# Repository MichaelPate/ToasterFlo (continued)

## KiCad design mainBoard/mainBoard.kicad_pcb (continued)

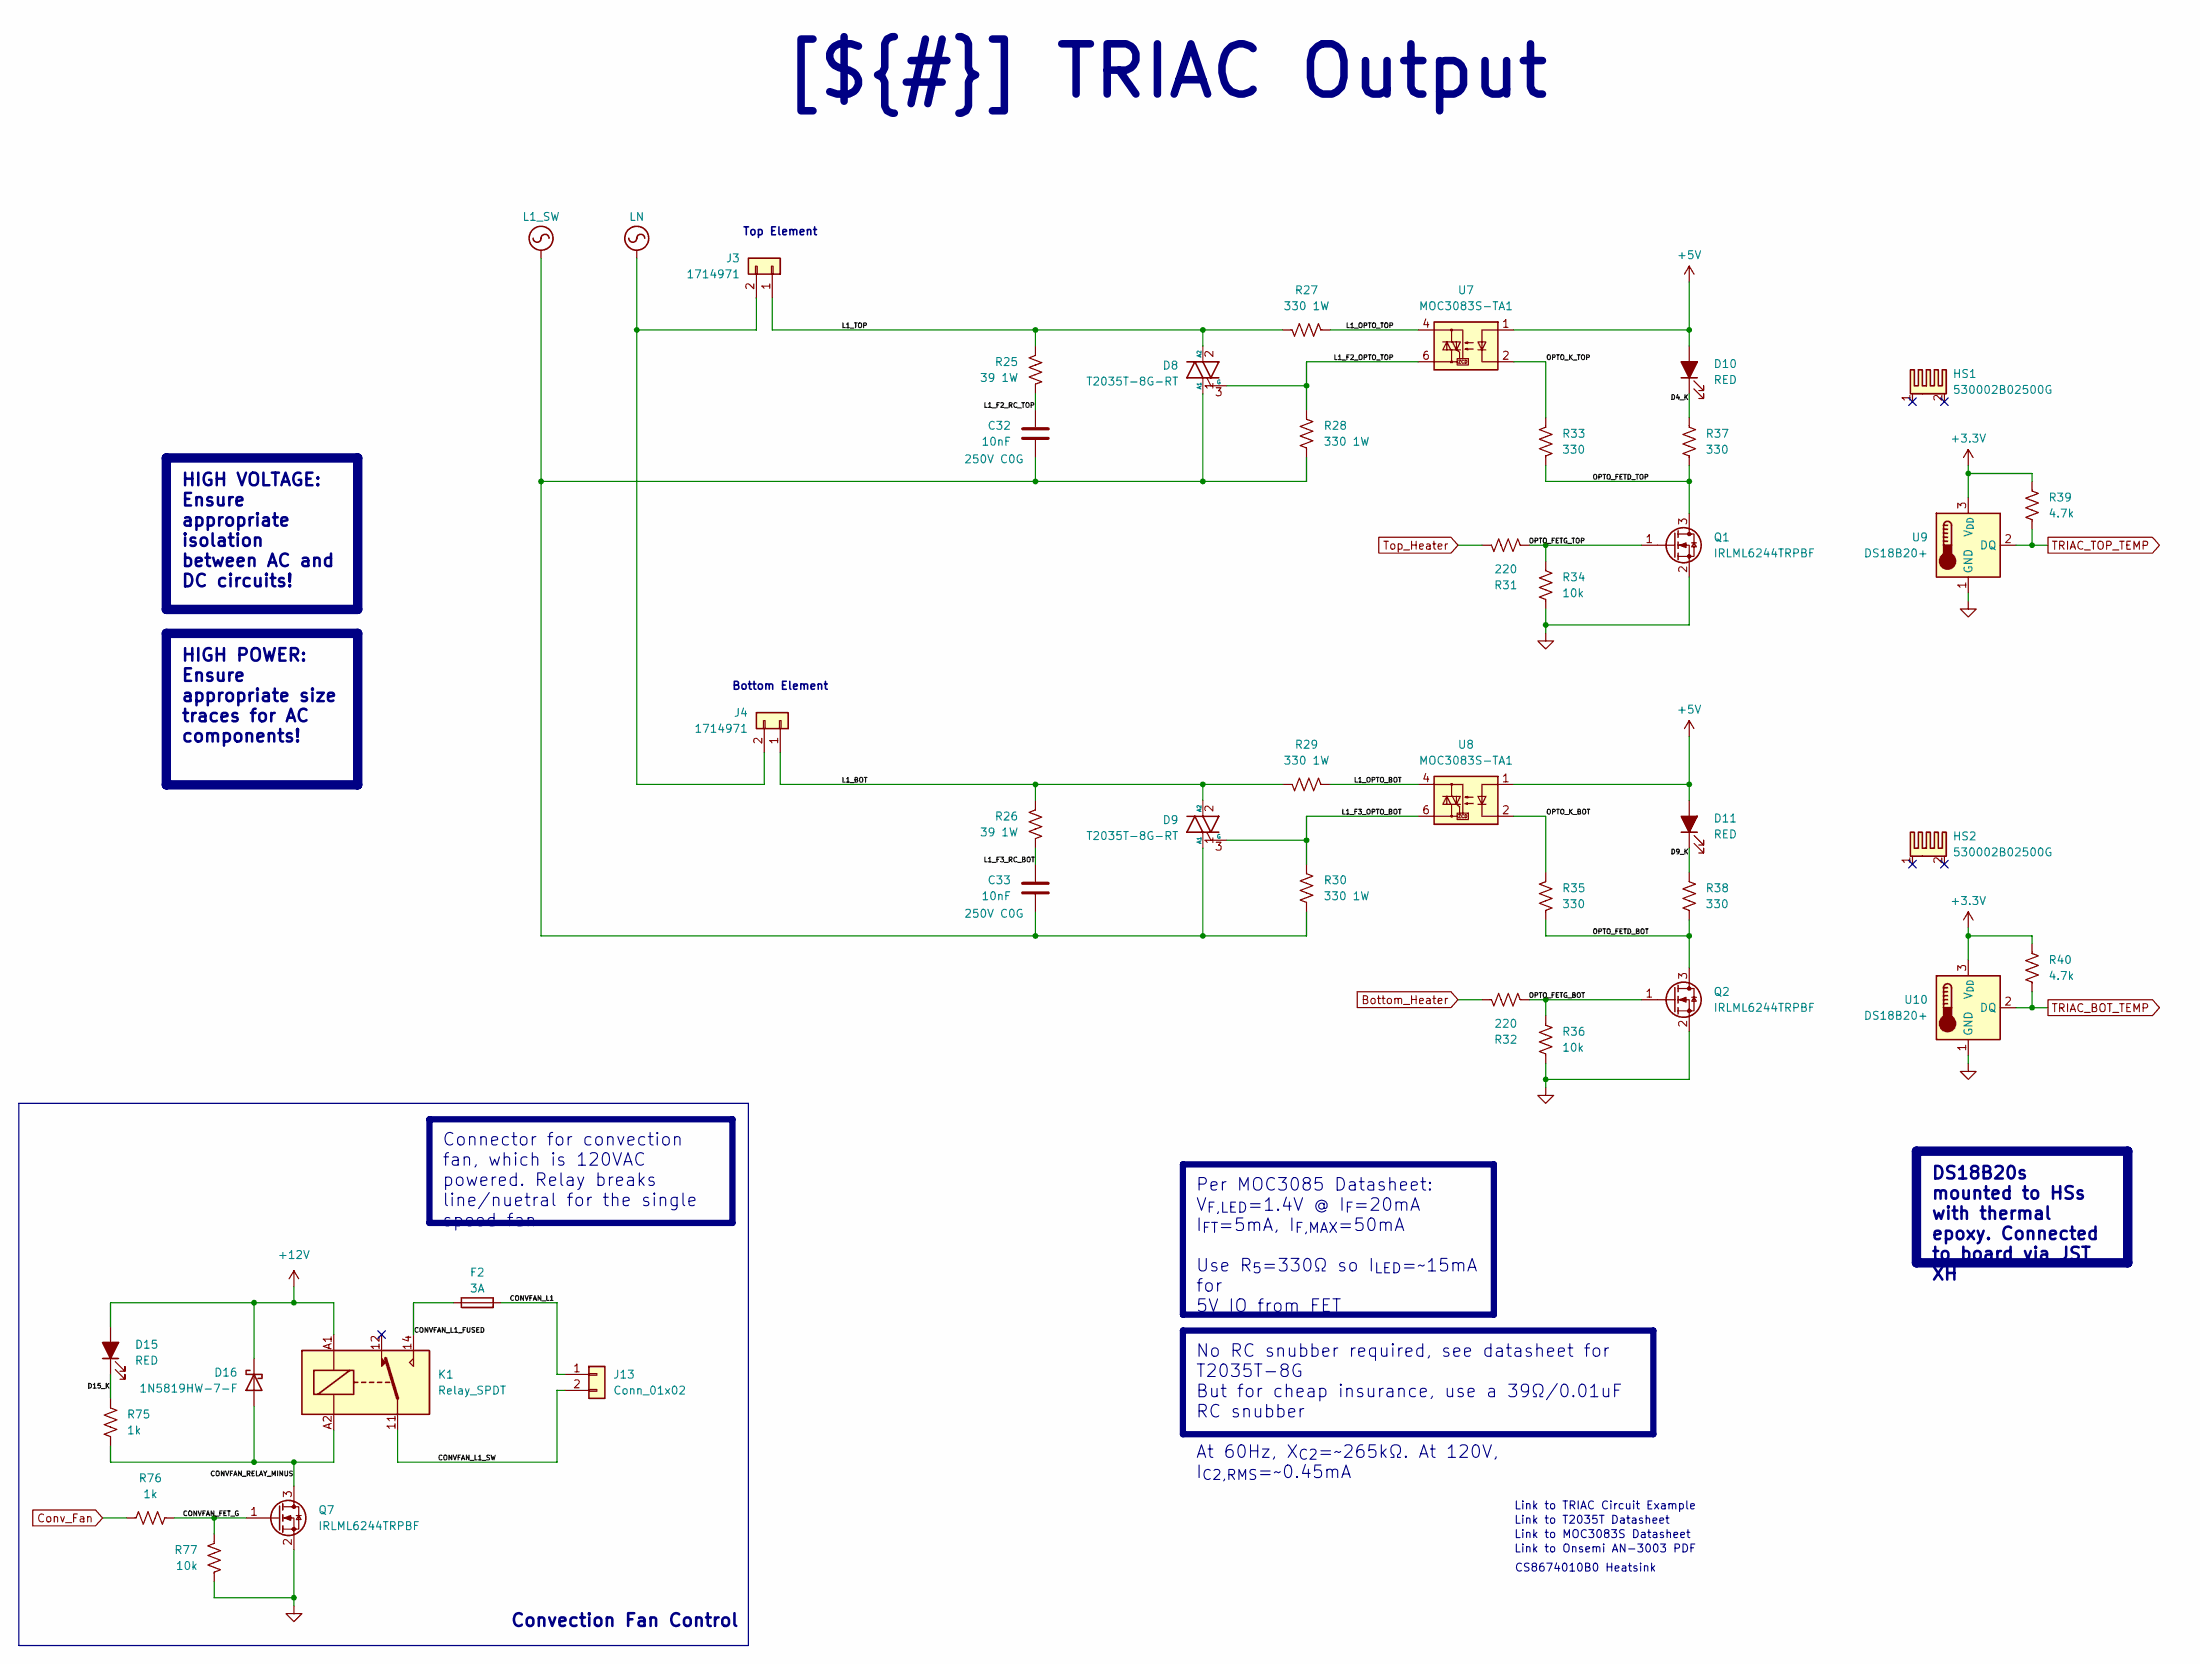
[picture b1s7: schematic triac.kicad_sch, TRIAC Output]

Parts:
C32, C33: 10nF; C_1812_4532Metric_Pad1.57x3.40mm_HandSolder
D8, D9: T2035T-8G-RT; TO-220-3_Vertical
D10, D11, D15: RED; LED_0603_1608Metric_Pad1.05x0.95mm_HandSolder
D16: 1N5819HW-7-F; D_SOD-123
F2: 3A; Fuseholder_Clip-5x20mm_Littelfuse_100_Inline_P20.50x4.60mm_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
HS1, HS2: 530002B02500G; 53002B02500G
J3, J4: 1714971; CONN_1714971_PXC
J13: Conn_01x02; CONN_1714971_PXC
K1: Relay_SPDT; Relay_SPDT_Finder_36.11
Q1, Q2, Q7: IRLML6244TRPBF; SOT-23
R25, R26: 39 1W; R_2512_6332Metric_Pad1.40x3.35mm_HandSolder
R27, R28, R29, R30: 330 1W; R_2512_6332Metric_Pad1.40x3.35mm_HandSolder
R31, R32: 220; R_0603_1608Metric_Pad0.98x0.95mm_HandSolder
R33, R35, R37, R38: 330; R_0603_1608Metric_Pad0.98x0.95mm_HandSolder
R34, R36, R77: 10k; R_0603_1608Metric_Pad0.98x0.95mm_HandSolder
R39, R40: 4.7k; R_0603_1608Metric_Pad0.98x0.95mm_HandSolder
R75, R76: 1k; R_0603_1608Metric_Pad0.98x0.95mm_HandSolder
U7, U8: MOC3083S-TA1; SMDIP-6_W9.53mm
U9, U10: DS18B20+; JST_XH_B3B-XH-A_1x03_P2.50mm_Vertical

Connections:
+3.3V: R39.1, R40.1, U9.3 (V_{DD}), U10.3 (V_{DD}); also elsewhere on the board
+5V: D10.2 (A), D11.2 (A), U7.1, U8.1; also elsewhere on the board
+12V: D15.2 (A), D16.1 (K), K1.A1; also elsewhere on the board
/Project Architecture/TRIAC/CONVFAN_FET_G: Q7.1 (G), R76.2, R77.1
/Project Architecture/TRIAC/CONVFAN_L1: F2.2, J13.1
/Project Architecture/TRIAC/CONVFAN_L1_FUSED: F2.1, K1.14
/Project Architecture/TRIAC/CONVFAN_L1_SW: J13.2, K1.11
/Project Architecture/TRIAC/CONVFAN_RELAY_MINUS: D16.2 (A), K1.A2, Q7.3 (D), R75.2
/Project Architecture/TRIAC/D4_K: D10.1 (K), R37.1
/Project Architecture/TRIAC/D9_K: D11.1 (K), R38.1
/Project Architecture/TRIAC/D15_K: D15.1 (K), R75.1
/Project Architecture/TRIAC/L1_BOT: D9.2 (A2), J4.1, R26.2, R29.2
/Project Architecture/TRIAC/L1_F2_OPTO_TOP: D8.3 (G), R28.2, U7.6
/Project Architecture/TRIAC/L1_F2_RC_TOP: C32.1, R25.1
/Project Architecture/TRIAC/L1_F3_OPTO_BOT: D9.3 (G), R30.2, U8.6
/Project Architecture/TRIAC/L1_F3_RC_BOT: C33.1, R26.1
/Project Architecture/TRIAC/L1_OPTO_BOT: R29.1, U8.4
/Project Architecture/TRIAC/L1_OPTO_TOP: R27.1, U7.4
/Project Architecture/TRIAC/L1_TOP: D8.2 (A2), J3.1, R25.2, R27.2
/Project Architecture/TRIAC/OPTO_FETD_BOT: Q2.3 (D), R35.2, R38.2
/Project Architecture/TRIAC/OPTO_FETD_TOP: Q1.3 (D), R33.2, R37.2
/Project Architecture/TRIAC/OPTO_FETG_BOT: Q2.1 (G), R32.2, R36.1
/Project Architecture/TRIAC/OPTO_FETG_TOP: Q1.1 (G), R31.2, R34.1
/Project Architecture/TRIAC/OPTO_K_BOT: R35.1, U8.2
/Project Architecture/TRIAC/OPTO_K_TOP: R33.1, U7.2
Bottom_Heater: R32.1
Conv_Fan: R76.1
GND: Q1.2 (S), Q2.2 (S), Q7.2 (S), R34.2, R36.2, R77.2, U9.1 (GND), U10.1 (GND); also elsewhere on the board
L1_SW: C32.2, C33.2, D8.1 (A1), D9.1 (A1), R28.1, R30.1; also elsewhere on the board
LN: J3.2, J4.2; also elsewhere on the board
TRIAC_BOT_TEMP: R40.2, U10.2 (DQ)
TRIAC_TOP_TEMP: R39.2, U9.2 (DQ)
Top_Heater: R31.1

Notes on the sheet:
Bottom Element
Link to T2035T Datasheet
Convection Fan Control
CS8674010B0 Heatsink
Link to Onsemi AN-3003 PDF
Top Element
Link to TRIAC Circuit Example
Link to MOC3083S Datasheet
HIGH POWER: Ensure appropriate size traces for AC components!
DS18B20s mounted to HSs with thermal epoxy. Connected to board via JST XH
[${#}] ${TITLE}
Connector for convection fan, which is 120VAC powered. Relay breaks line/nuetral for the single speed fan
HIGH VOLTAGE: Ensure appropriate isolation between AC and DC circuits!
No RC snubber required, see datasheet for T2035T-8G But for cheap insurance, use a 39Ω/0.01uF RC snubber At 60Hz, X_{C2}=~265kΩ. At 120V, I_{C2,RMS}=~0.45mA
Per MOC3085 Datasheet: V_{F,LED}=1.4V @ I_{F}=20mA I_{FT}=5mA, I_{F,MAX}=50mA Use R_{5}=330Ω so I_{LED}=~15mA for 5V IO from FET

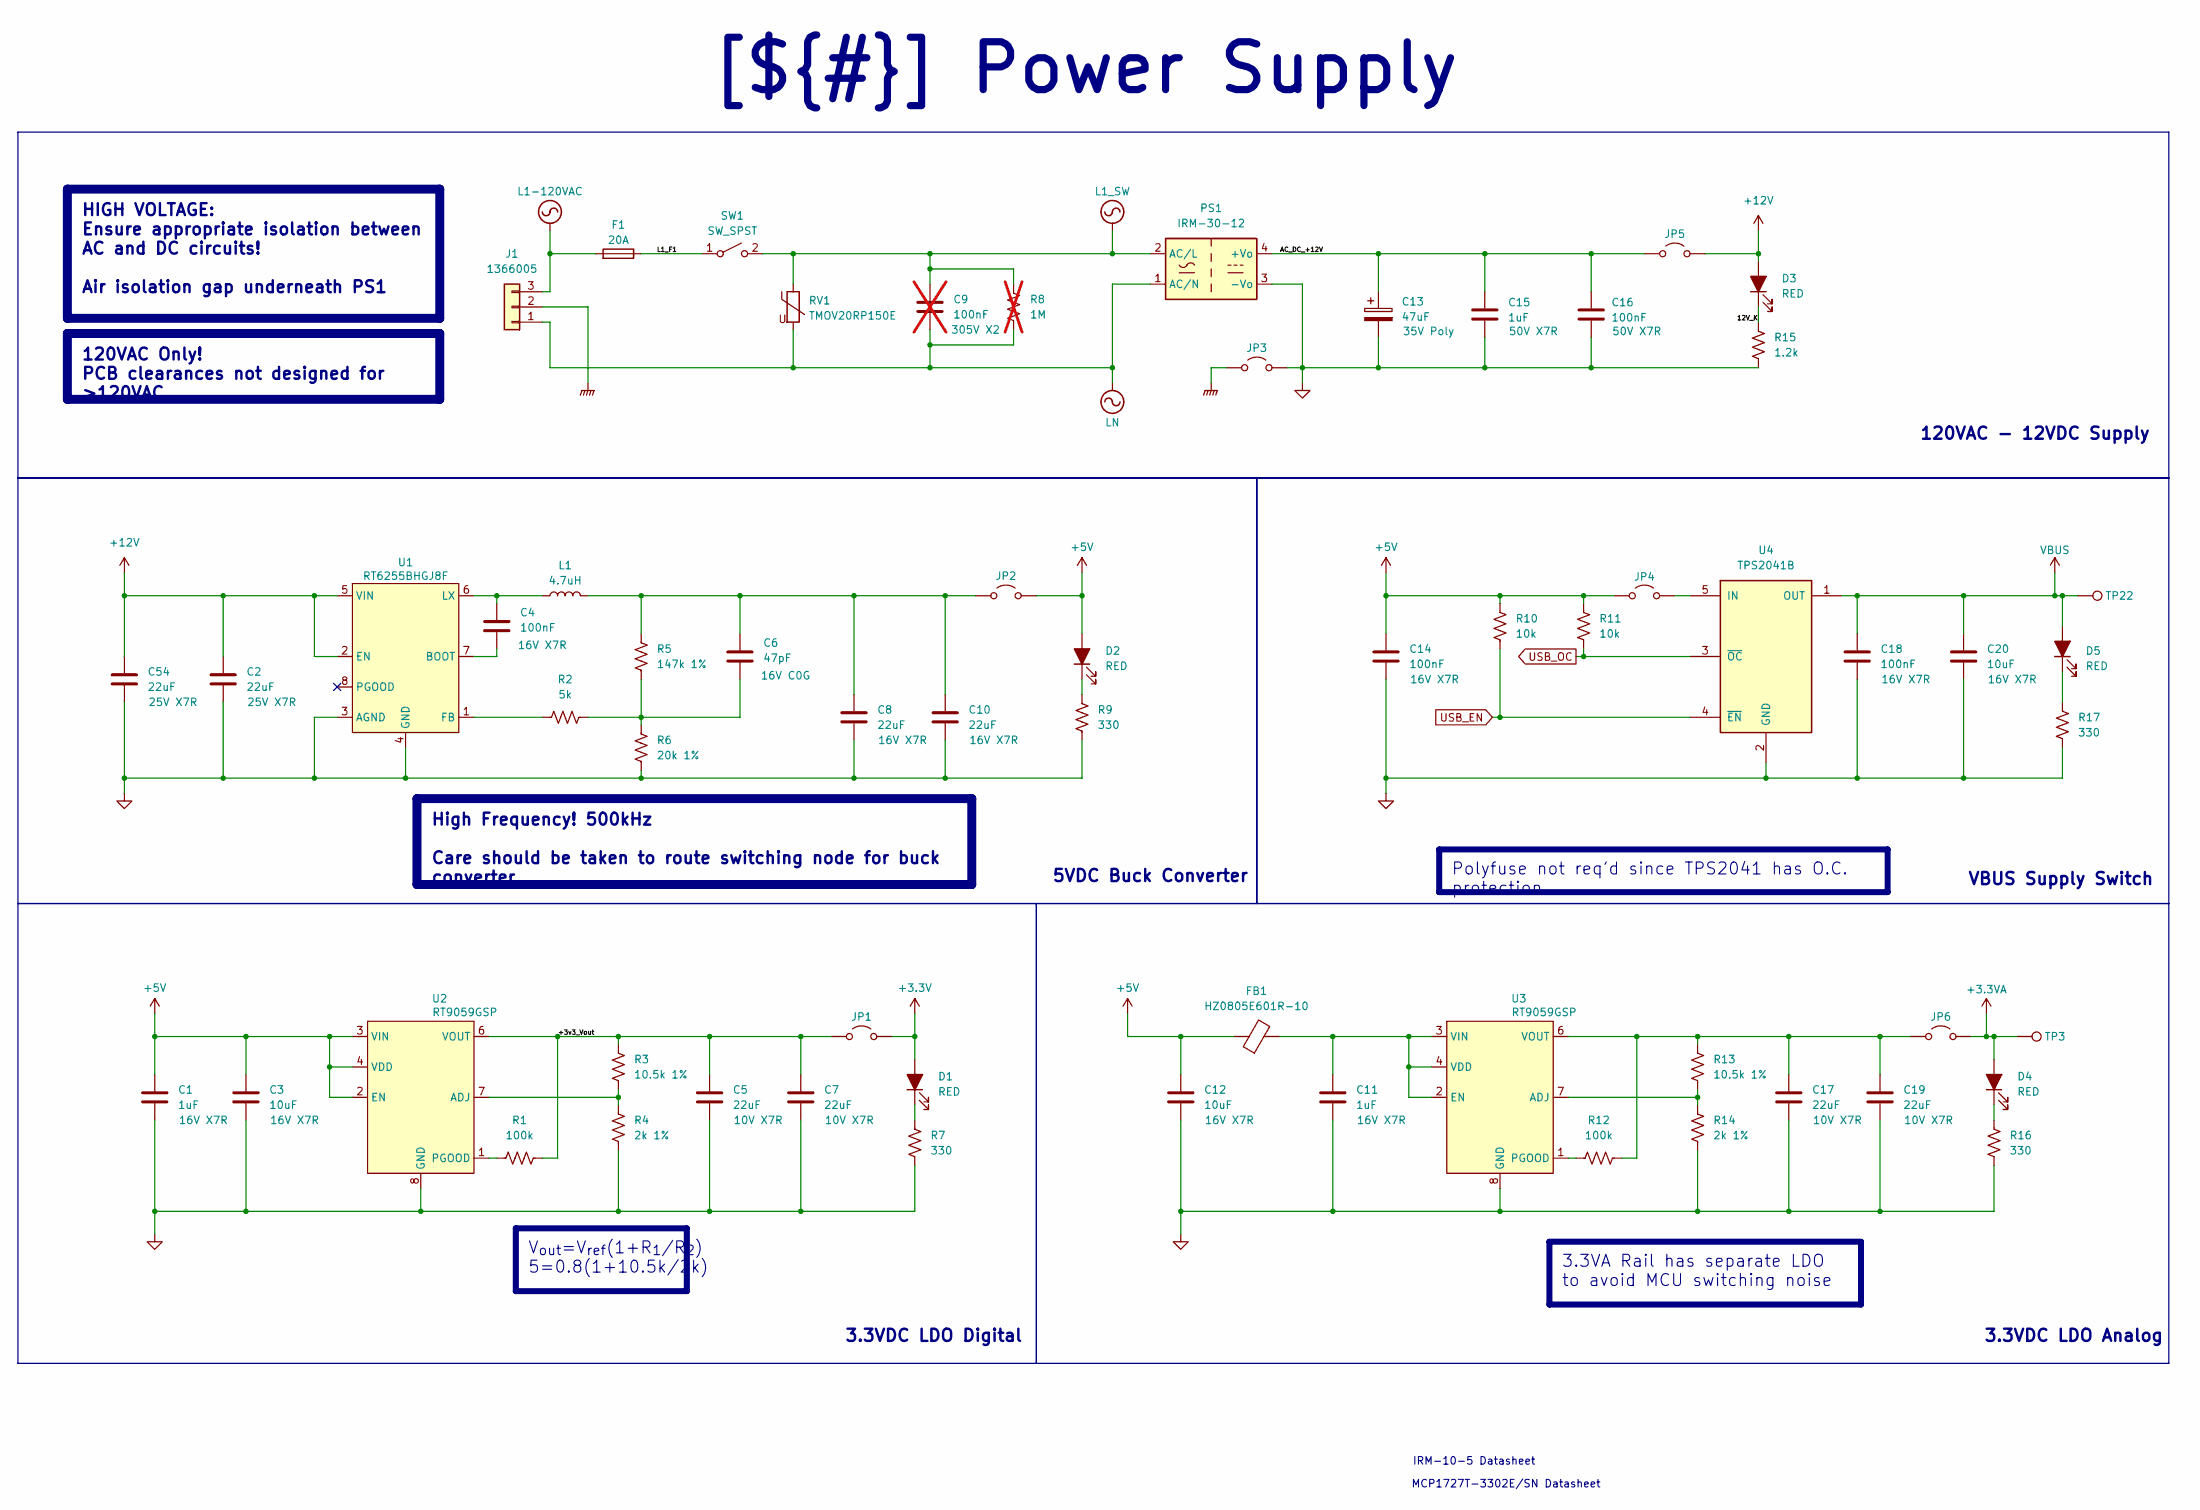
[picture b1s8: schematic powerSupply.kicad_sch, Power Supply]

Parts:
C1, C11: 1uF; C_0805_2012Metric_Pad1.18x1.45mm_HandSolder; part number CL31A226MOCLNNC
C2, C8, C10, C54: 22uF; C_1206_3216Metric_Pad1.33x1.80mm_HandSolder; part number CL31A226MOCLNNC
C3, C12: 10uF; C_0805_2012Metric_Pad1.18x1.45mm_HandSolder; part number CL31A226MOCLNNC
C4: 100nF; C_0402_1005Metric_Pad0.74x0.62mm_HandSolder
C5, C7, C17, C19: 22uF; C_0805_2012Metric_Pad1.18x1.45mm_HandSolder; part number CL31A226MOCLNNC
C6: 47pF; C_0603_1608Metric_Pad1.08x0.95mm_HandSolder
C9: 100nF; C_Rect_L18.0mm_W5.0mm_P15.00mm_FKS3_FKP3; part number B32922C3104M189; not fitted
C13: 47uF; C_Elec_6.3x5.8; part number A768EB476M1VLAE042
C14, C16, C18: 100nF; C_0603_1608Metric_Pad1.08x0.95mm_HandSolder
C15: 1uF; C_0805_2012Metric_Pad1.18x1.45mm_HandSolder; part number CL21B105KAFNNNE
C20: 10uF; C_0603_1608Metric_Pad1.08x0.95mm_HandSolder
D1, D2, D3, D4, D5: RED; LED_0603_1608Metric_Pad1.05x0.95mm_HandSolder
F1: 20A; Fuseholder_Clip-6.3x32mm_Littelfuse_122_Inline_P34.21x7.62m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
FB1: HZ0805E601R-10; L_0805_2012Metric_Pad1.05x1.20mm_HandSolder
J1: 1366005; CONN_1714984_PXC
JP1, JP2, JP4, JP5, JP6: Jumper_2_Open; PinHeader_1x02_P2.54mm_Vertical
JP3: Jumper_2_Open; SolderJumper-2_P1.3mm_Open_TrianglePad1.0x1.5mm
L1: 4.7uH; L_Coilcraft_XAL7030-472; part number 7440700047
PS1: IRM-30-12; IRM-30_MWU
R1, R12: 100k; R_0603_1608Metric_Pad0.98x0.95mm_HandSolder
R2: 5k; R_0603_1608Metric_Pad0.98x0.95mm_HandSolder
R3, R13: 10.5k 1%; R_0603_1608Metric_Pad0.98x0.95mm_HandSolder
R4, R14: 2k 1%; R_0603_1608Metric_Pad0.98x0.95mm_HandSolder
R5: 147k 1%; R_0603_1608Metric_Pad0.98x0.95mm_HandSolder
R6: 20k 1%; R_0603_1608Metric_Pad0.98x0.95mm_HandSolder
R7, R9, R16, R17: 330; R_0603_1608Metric_Pad0.98x0.95mm_HandSolder
R8: 1M; R_2512_6332Metric_Pad1.40x3.35mm_HandSolder; not fitted
R10, R11: 10k; R_0603_1608Metric_Pad0.98x0.95mm_HandSolder
R15: 1.2k; R_0603_1608Metric_Pad0.98x0.95mm_HandSolder
RV1: TMOV20RP150E
SW1: SW_SPST; CONN_1714971_PXC
TP3: TestPoint; TestPoint_Pad_2.0x2.0mm
TP22: TestPoint; TestPoint_Pad_D2.0mm
U1: RT6255BHGJ8F; TSOT-23-8
U2, U3: RT9059GSP; SOP-8-1EP_4.57x4.57mm_P1.27mm_EP4.57x4.45mm
U4: TPS2041B; SOT-23-5

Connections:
+3.3V: D1.2 (A), JP1.2 (B); also elsewhere on the board
+3.3VA: D4.2 (A), JP6.2 (B), TP3.1 (1_1); also elsewhere on the board
+5V: C1.1, C3.1, C12.1, C14.1, D2.2 (A), FB1.1, JP2.2 (B), JP4.1 (A), R10.2, R11.2, U2.2 (EN), U2.3 (VIN), U2.4 (VDD); also elsewhere on the board
+12V: C2.1, C54.1, D3.2 (A), JP5.2 (B), U1.2 (EN), U1.5 (VIN); also elsewhere on the board
/Project Architecture/Power Supply/12V_K: D3.1 (K), R15.1
/Project Architecture/Power Supply/+3v3_Vout: C5.1, C7.1, JP1.1 (A), R1.2, R3.1, U2.6 (VOUT)
/Project Architecture/Power Supply/AC_DC_+12V: C13.1, C15.1, C16.1, JP5.1 (A), PS1.4 (+Vo)
/Project Architecture/Power Supply/L1_F1: F1.1, SW1.1 (A)
GND: C1.2, C2.2, C3.2, C5.2, C7.2, C8.2, C10.2, C11.2, C12.2, C13.2, C14.2, C15.2, C16.2, C17.2, C18.2, C19.2, C20.2, C54.2, JP3.2 (B), PS1.3 (-Vo), R4.2, R6.2, R7.2, R9.2, R14.2, R15.2, R16.2, R17.2, U1.3 (AGND), U1.4 (GND), U2.8 (GND), U3.8 (GND), U4.2 (GND); also elsewhere on the board
GNDPWR: J1.2, JP3.1 (A); also elsewhere on the board
L1-120VAC: F1.2, J1.3
L1_SW: C9.1, PS1.2 (AC/L), R8.2, RV1.1, SW1.2 (B); also elsewhere on the board
LN: C9.2, J1.1, PS1.1 (AC/N), R8.1, RV1.2; also elsewhere on the board
unnamed: C6.2, R2.2, R5.2, R6.1
unnamed: D1.1 (K), R7.1
unnamed: D2.1 (K), R9.1
unnamed: D4.1 (K), R16.1
unnamed: D5.1 (K), R17.1
unnamed: C6.1, C8.1, C10.1, JP2.1 (A), L1.2, R5.1
unnamed: JP4.2 (B), U4.5 (IN)
unnamed: C17.1, C19.1, JP6.1 (A), R12.2, R13.1, U3.6 (VOUT)
unnamed: C4.2, U1.7 (BOOT)
unnamed: R2.1, U1.1 (FB)
unnamed: C4.1, L1.1, U1.6 (LX)
unnamed: R3.2, R4.1, U2.7 (ADJ)
unnamed: R1.1, U2.1 (PGOOD)
unnamed: R13.2, R14.1, U3.7 (ADJ)
unnamed: C11.1, FB1.2, U3.2 (EN), U3.3 (VIN), U3.4 (VDD)
unnamed: R12.1, U3.1 (PGOOD)
USB_EN: R10.1, U4.4 (~EN)
USB_OC: R11.1, U4.3 (~OC)
VBUS: C18.1, C20.1, D5.2 (A), TP22.1 (1_1), U4.1 (OUT); also elsewhere on the board

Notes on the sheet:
3.3VDC LDO Analog
120VAC - 12VDC Supply
3.3VDC LDO Digital
VBUS Supply Switch
IRM-10-5 Datasheet
MCP1727T-3302E/SN Datasheet
5VDC Buck Converter
120VAC Only! PCB clearances not designed for >120VAC
[${#}] ${TITLE}
Polyfuse not req'd since TPS2041 has O.C. protection
High Frequency! 500kHz Care should be taken to route switching node for buck converter
HIGH VOLTAGE: Ensure appropriate isolation between AC and DC circuits! Air isolation gap underneath PS1
3.3VA Rail has separate LDO to avoid MCU switching noise
V_{out}=V_{ref}(1+R_{1}/R_{2}) 5=0.8(1+10.5k/2k)

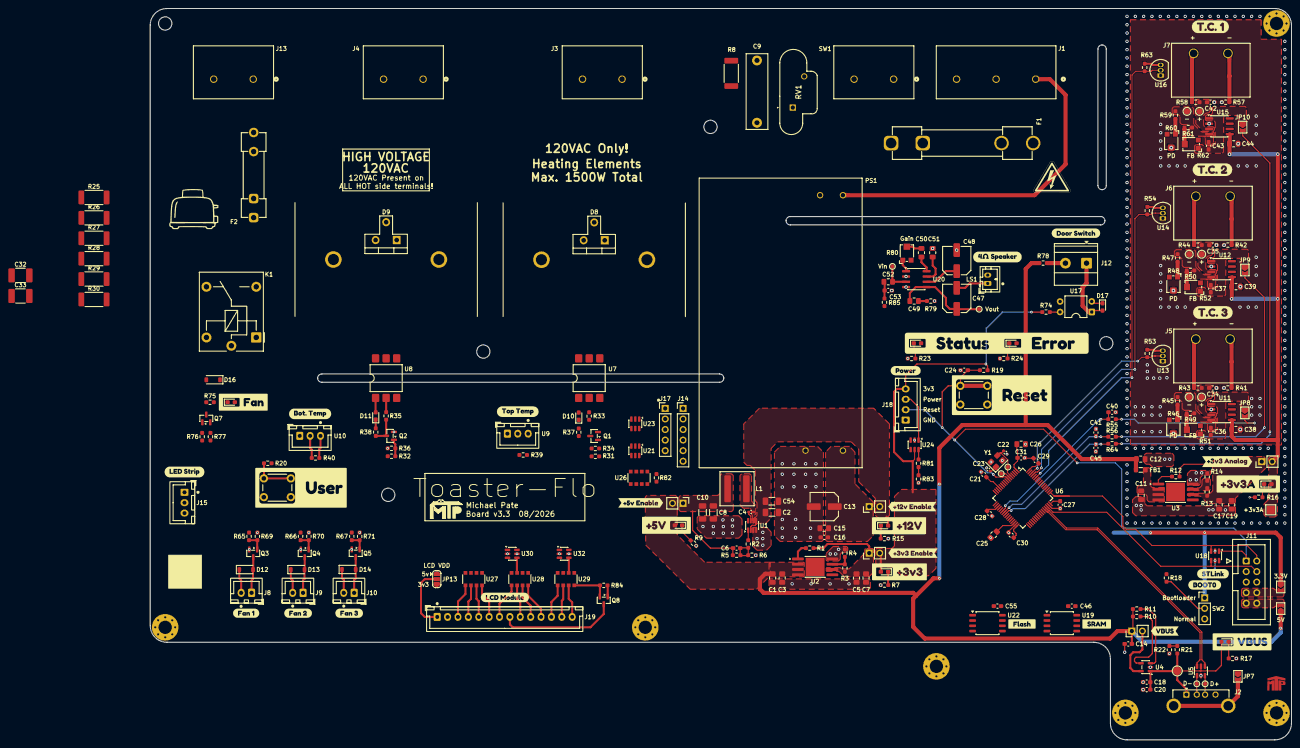
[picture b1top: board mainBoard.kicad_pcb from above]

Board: 4 copper layers, 274.8 x 176.1 mm, 293 parts (1 on the bottom side), 156 nets.

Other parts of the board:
kobee-studio-6A7A4227: Kobee Studio; kobee-studio-6A7A4227
kobee-studio-6A8DB43B, kobee-studio-6A90DB5E, kobee-studio-6A90DB6E, kobee-studio-6A90DB75, kobee-studio-6A90DB86, kobee-studio-6A9102A2: Kobee Studio; kobee-studio-6A8DB43B
kobee-studio-6A8DB157, kobee-studio-6A921F60, kobee-studio-6A922012: Kobee Studio; kobee-studio-6A788950
kobee-studio-6A8DB453: Kobee Studio; kobee-studio-6A8DB453
kobee-studio-6A8E052B: Kobee Studio; kobee-studio-6A8E0501
kobee-studio-6A8E0510: Kobee Studio; kobee-studio-6A8E0510
kobee-studio-6A8F1C14: Kobee Studio; kobee-studio-6A8F1C14
kobee-studio-6A8F2A61, kobee-studio-6A78A703, kobee-studio-6A90DFD2: Kobee Studio; kobee-studio-6A78A5D5
kobee-studio-6A8F1652: Kobee Studio; kobee-studio-6A8DB219
kobee-studio-6A8F1659: Kobee Studio; kobee-studio-6A8DB208
kobee-studio-6A8F1662: Kobee Studio; kobee-studio-6A8DB1E2
kobee-studio-6A78A6FA: Kobee Studio; kobee-studio-6A78A483
kobee-studio-6A78A34B: Kobee Studio; kobee-studio-6A788922
kobee-studio-6A78A548: Kobee Studio; kobee-studio-6A78A4EC
kobee-studio-6A78A618: Kobee Studio; kobee-studio-6A78A618
kobee-studio-6A78B9B1: Kobee Studio; kobee-studio-6A78B9B1
kobee-studio-6A78B988: Kobee Studio; kobee-studio-6A78B988
kobee-studio-6A919D0F, kobee-studio-6A919D24: Kobee Studio; kobee-studio-6A919D0F
kobee-studio-6A7920CC: Kobee Studio; kobee-studio-6A7920CC
kobee-studio-6A79213B: Kobee Studio; kobee-studio-6A791FA5
kobee-studio-6A79225D: Kobee Studio; kobee-studio-6A791EC5

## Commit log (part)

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2026-06-10 Add revision 1 schematics
2026-06-10 Add library files from rev 1
2026-06-10 Update netclasses
2026-06-13 Add net colors and tweak MCU
2026-06-17 Schematic Capture should be complete, ready for PCB
2026-06-18 tweak schematic for changes from 6-17-2026
    major structural changes, see daily note from obsidian
2026-06-20 work on pcb design
2026-06-20 working on pcb layout after bringing in work from laptop
2026-06-20 update project to kicad 10
2026-06-23 board routing nearly complete
2026-06-27 tweak board design more
2026-06-27 3d models added to PCB
2026-06-29 board tweaked, sent for review
2026-06-30 reworked AC switching and fusing
2026-06-30 change to C0G caps for thermocouple amps
2026-06-30 Add ESD protection to headers
2026-06-30 change to cheaper ESD TVS diodes
2026-06-30 Add pullup resistors to digital thermometers
